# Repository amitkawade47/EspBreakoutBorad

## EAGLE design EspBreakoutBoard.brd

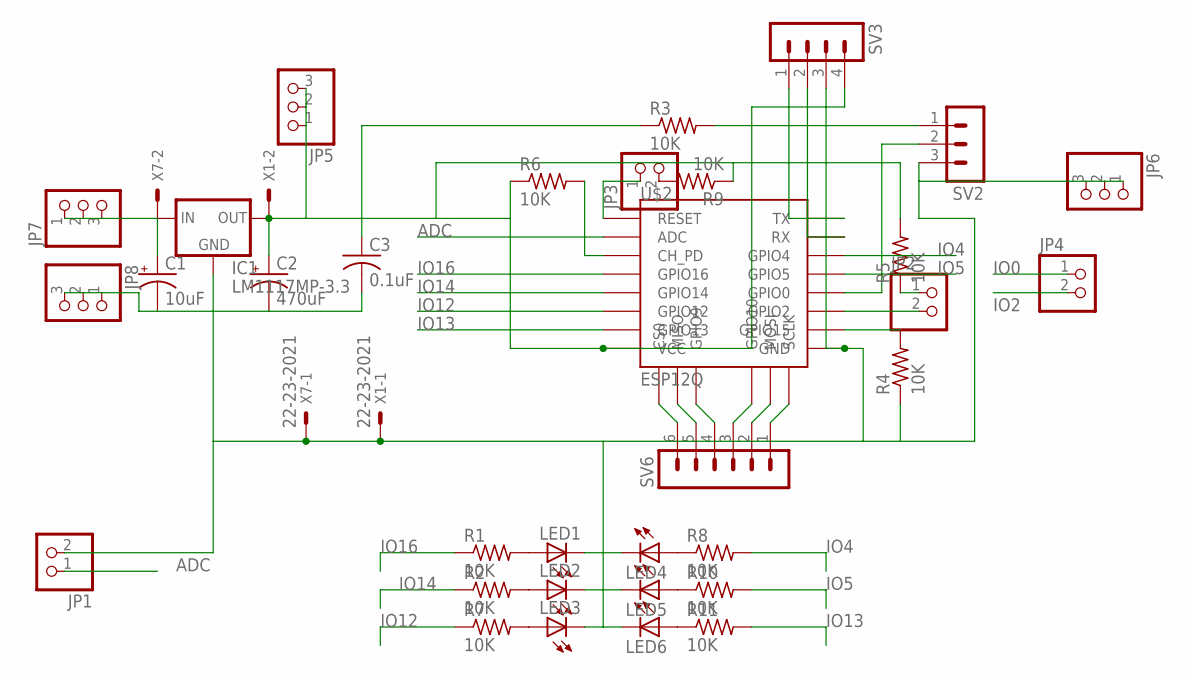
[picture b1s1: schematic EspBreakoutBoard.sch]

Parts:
C1: 10uF; E2,5-6
C2: 470uF; E5-8,5
C3: 0.1uF; C025-040X050
IC1: LM1117MP-3.3; SOT223
JP1, JP2, JP3, JP4: PINHD-1X2; 1X02
JP5, JP6, JP7, JP8: PINHD-1X3; 1X03
LED1, LED2, LED3, LED4, LED5, LED6: LED3MM
R1, R2, R3, R4, R5, R6, R7, R8, R9, R10, R11: 10K; 0207/10
SV2: MA03-1
SV3: MA04-1
SV6: MA06-1
U$2: ESP12Q
X1, X7: 22-23-2021

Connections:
5V1: C1.+, IC1.3 (IN), JP7.1, JP7.2, JP7.3, X7.2
ADC: JP1.1, U$2.ADC
GND: C1.-, C2.-, C3.2, IC1.1 (GND), JP1.2, JP6.1, JP6.2, JP6.3, JP8.1, JP8.2, JP8.3, LED1.K (C), LED2.K (C), LED3.K (C), LED4.K (C), LED5.K (C), LED6.K (C), R4.1, SV2.3, SV3.3, U$2.GND, X1.1, X7.1
IO0: JP4.1, SV2.2, U$2.GPIO0
IO2: JP2.2, JP4.2, U$2.GPIO2
IO4: R8.2, U$2.GPIO4
IO5: R10.2, U$2.GPIO5
IO12: R7.1, U$2.GPIO12
IO13: R11.2, U$2.GPIO13
IO14: R2.1, U$2.GPIO14
IO16: R1.1, U$2.GPIO16
unnamed: JP2.1, R5.1
unnamed: JP3.2, R9.2
unnamed: JP3.1, U$2.RESET
unnamed: R3.2, SV2.1
unnamed: R4.2, U$2.GPIO15
unnamed: SV3.1, U$2.TX
unnamed: SV3.2, U$2.RX
unnamed: R6.2, U$2.CH_PD
unnamed: C2.+, C3.1, IC1.2 (OUT), IC1.4 (OUT), JP5.1, JP5.2, JP5.3, R3.1, R5.2, R6.1, R9.1, SV3.4, U$2.VCC, X1.2
unnamed: LED1.A, R1.2
unnamed: LED2.A, R2.2
unnamed: LED3.A, R7.2
unnamed: LED4.A, R8.1
unnamed: LED5.A, R10.1
unnamed: LED6.A, R11.1
unnamed: SV6.1, U$2.SCLK
unnamed: SV6.4, U$2.GPIO9
unnamed: SV6.5, U$2.MISO
unnamed: SV6.6, U$2.CS0
unnamed: SV6.2, U$2.MOSI
unnamed: SV6.3, U$2.GPIO10

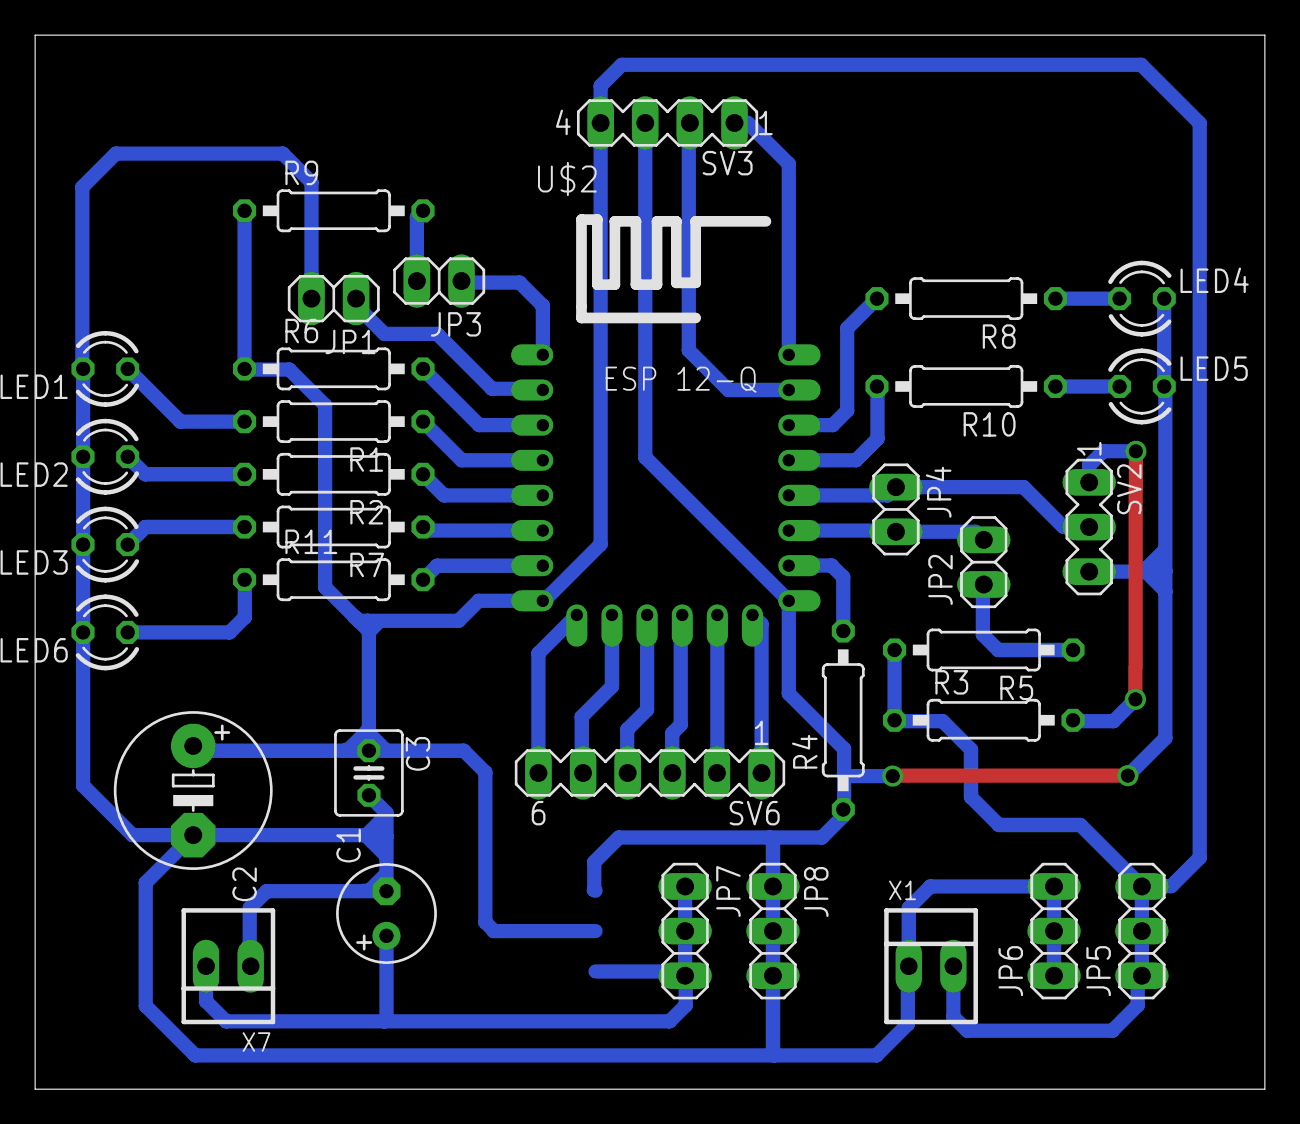
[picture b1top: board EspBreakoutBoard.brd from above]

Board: 2 copper layers, 70.0 x 60.0 mm, 35 parts (1 on the bottom side), 32 nets.

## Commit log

2018-02-18 Esp Breakout Board
    board designed for boot mode as well as program mode.
    added jumper for GPIO0 and GPIO2
2018-02-18 Board layout in pdf
    board layout in pdf format added.
